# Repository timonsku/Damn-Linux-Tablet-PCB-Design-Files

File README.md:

DLT - A Damn Linux Tablet
==========
PCB Design Files
-----
Collection of PCB and CAD design files for DLT ( https://hackaday.io/project/164845-dlt-one-a-damn-linux-tablet ).
This project is currently in its early stages and none of the files hosted here are necessarily fully tested, they might work but only to the extent I need them to, some features that I have not tried might not work.
I uploaded them anyway at this stage for documentation purposes and for those that are curious.

All works are licensed under CC BY-SA 4.0.

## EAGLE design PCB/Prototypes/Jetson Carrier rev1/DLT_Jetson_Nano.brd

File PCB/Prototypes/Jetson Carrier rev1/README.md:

Be aware this a prototype!
====

This means there might be issues with this board.
All peripherals have been tested and are working on this revision, it is mostly based on AntMicros schematics of their open source carrier design.
Still, you might find something not working for you, no gurantees so proceed with caution.

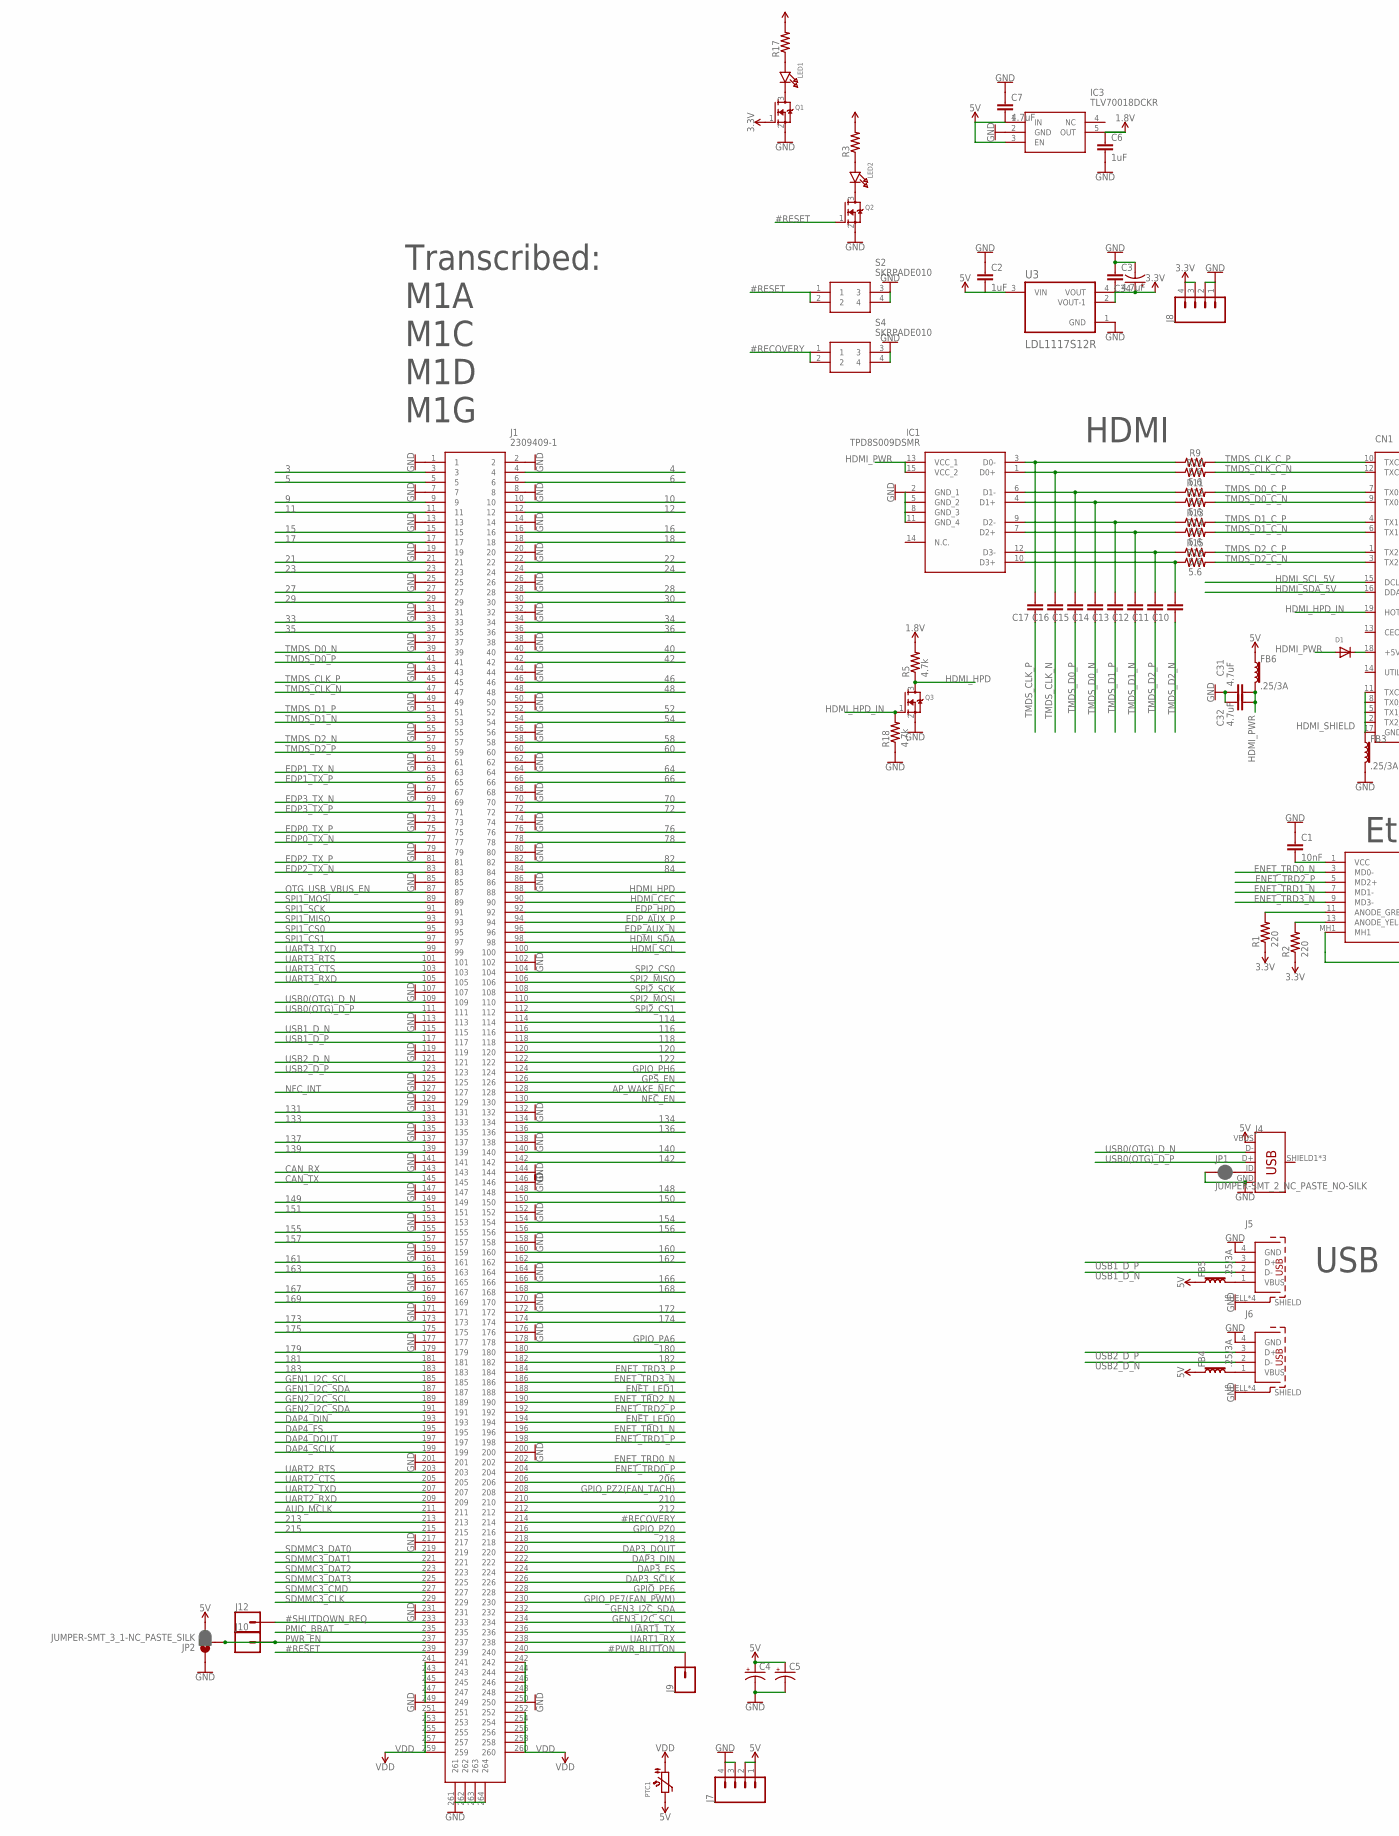
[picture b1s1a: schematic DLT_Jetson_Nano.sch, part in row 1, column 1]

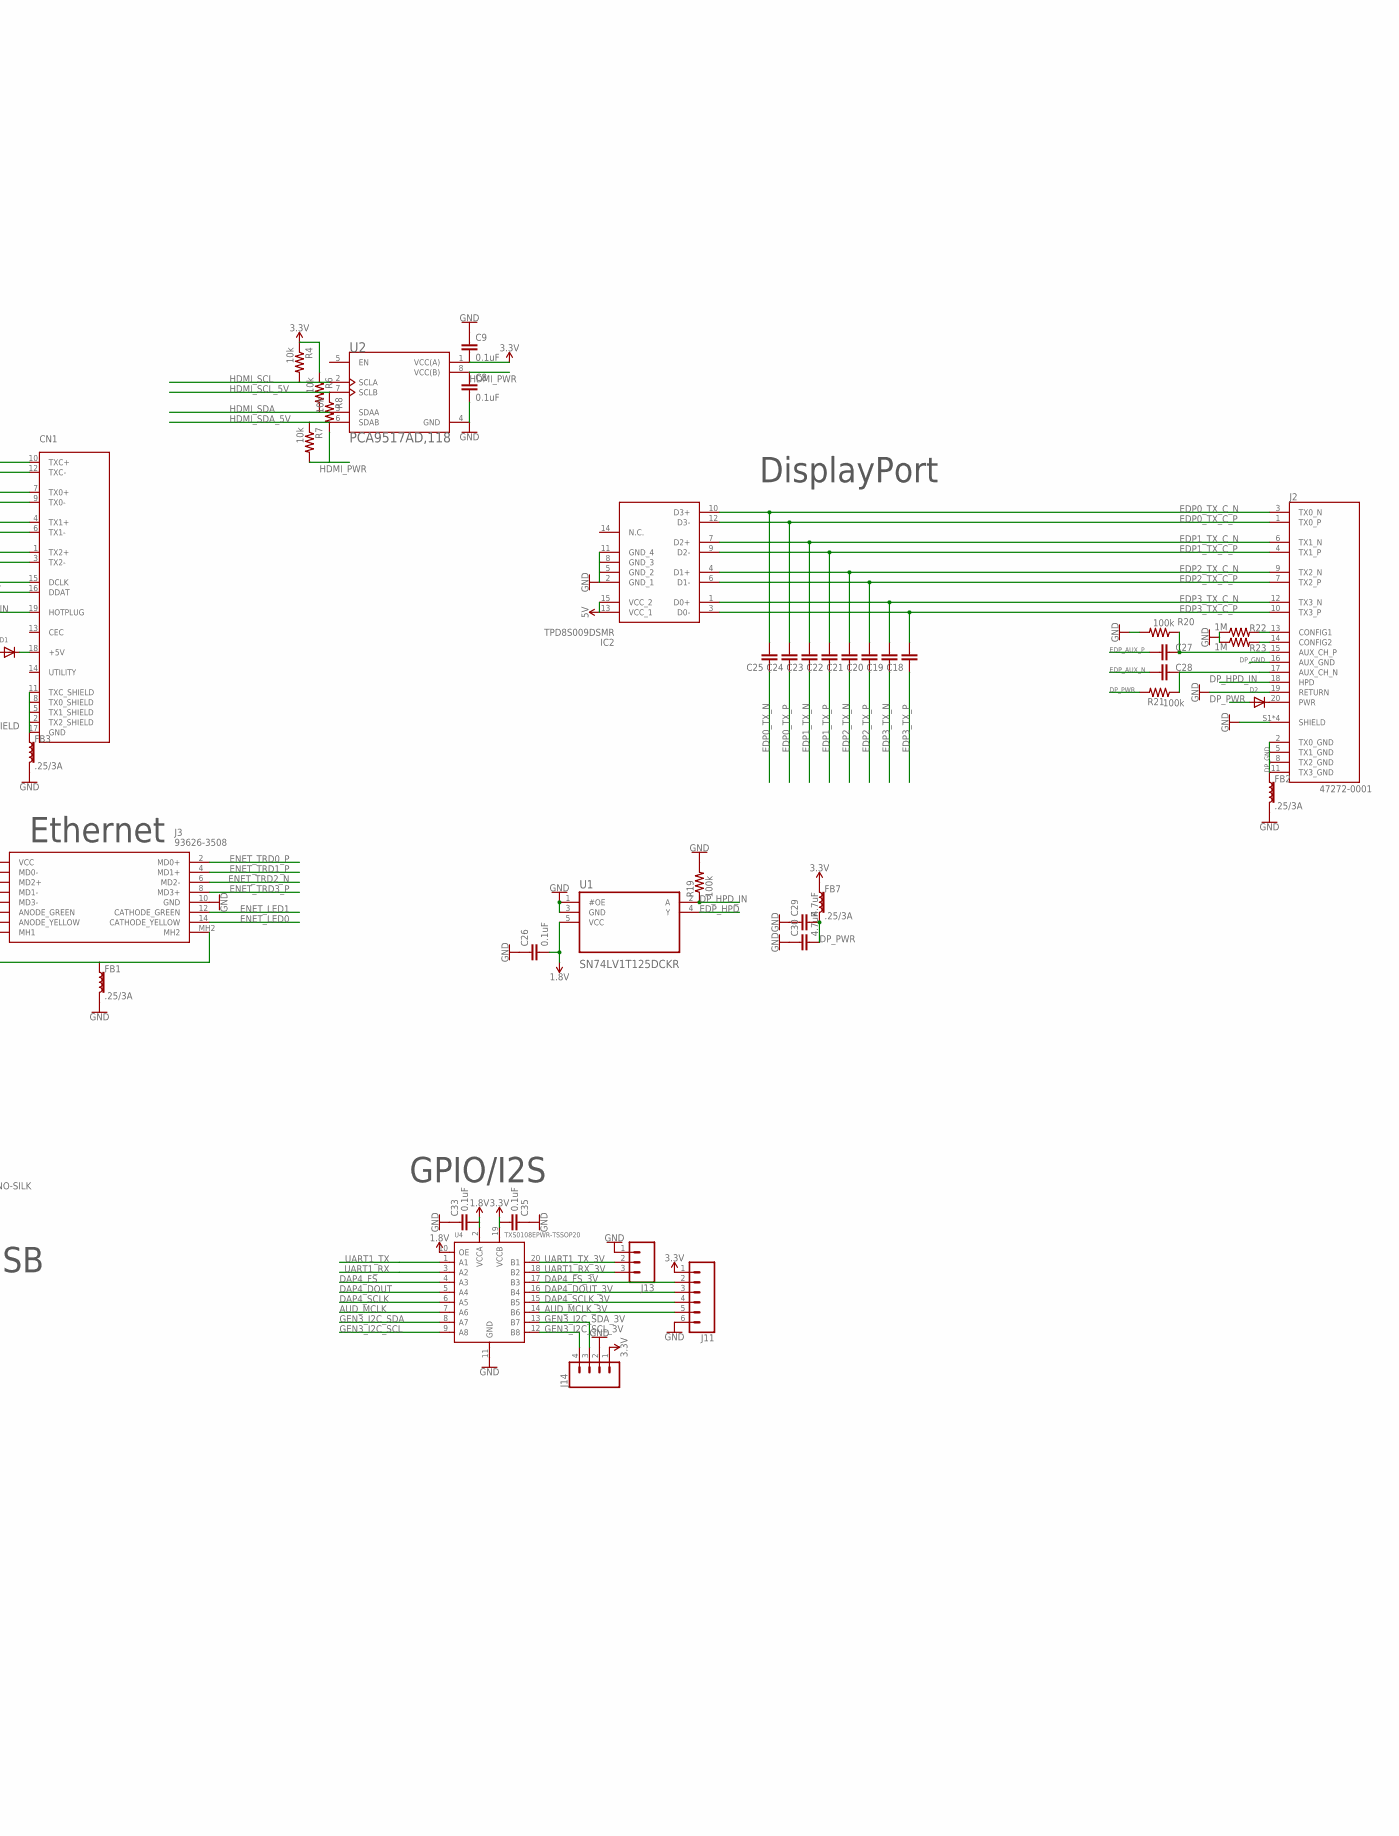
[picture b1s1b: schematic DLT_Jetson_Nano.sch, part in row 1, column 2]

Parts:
C1: 10nF; 0603
C2, C6: 1uF; 0603
C3, C7, C29, C30, C31, C32: 4.7uF; 0603
C4, C5, C34: CAP_POLD; PANASONIC_D
C8, C9, C26, C33, C35: 0.1uF; 0603
C10, C11, C12, C13, C14, C15, C16, C17, C18, C19, C20, C21, C22, C23, C24, C25, C27, C28: 0.1uF; 0402
CN1: HDMI_MOLEX_47151-0001
D1, D2: DIODESMA; SMADIODE
FB1, FB2, FB3, FB4, FB5, FB6, FB7: .25/3A; 0603
IC1, IC2: TPD8S009DSMR
IC3: TLV70018DCKR; SOT65P210X110-5N
J1: 2309409-1
J2: 47272-0001; MOLEX_47272-0001
J3: 93626-3508; 936263508
J4: USB_MICRO-B_FEMALE-SMT; USB-B-MICRO-SMD
J5, J6: 629104190121
J7, J8: CONN_04LOCK_LONGPADS; 1X04_LOCK_LONGPADS
J9, J10, J12: CONN_01; 1X01
J11: CONN_06SILK_FEMALE_PTH; 1X06
J13: CONN_03; 1X03
J14: CONN_04; 1X04
JP1: JUMPER-SMT_2_NC_PASTE_NO-SILK; SMT-JUMPER_2_NC_PASTE_NO-SILK
JP2: JUMPER-SMT_3_1-NC_PASTE_SILK; SMT-JUMPER_3_1-NC_PASTE_SILK
LED1, LED2: LED0805; CHIPLED_0805
PTC1: PTC1206; 1206
Q1, Q2, Q3: MOSFET-NWAVE; SOT23-W
R1, R2: 220; 0805
R3, R17: RESISTOR0805-RES; 0805
R4, R6, R7, R8: 10k; 0805
R5, R18: 4.7k; 0805
R9, R10, R11, R12, R13, R14, R15, R16: 5.6; 0402
R19, R20, R21: 100k; 0805
R22, R23: 1M; 0805
S2, S4: SKRPADE010
U1: SN74LV1T125DCKR; SOT65P210X110-5N
U2: PCA9517AD,118; SOIC127P600X175-8N
U3: LDL1117S12R; SOT230P700X180-4N
U4: TXS0108EPWR-TSSOP20; TSSOP20-0.65-6.5X4.4MM

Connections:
1.8V: C6.1, C26.2, C33.2, IC3.5 (OUT), R5.2, U1.5 (VCC), U4.2 (VCCA), U4.10 (OE)
3: J1.3
3.3V: C3.2, C9.2, C34.+, C35.1, FB7.1, J8.3, J8.4, J11.1, J14.1, Q1.1 (G), R1.1, R2.1, R4.1, R6.1, U2.1 (VCC(A)), U3.2 (VOUT-1), U3.4 (VOUT), U4.19 (VCCB)
4: J1.4
5: J1.5
5V: C2.2, C4.+, C5.+, C7.2, FB4.1, FB5.1, FB6.1, IC2.13 (VCC_1), IC2.15 (VCC_2), IC3.1 (IN), IC3.3 (EN), J4.VBUS, J7.1, J7.2, JP2.3, PTC1.2, R3.2, R17.2, U3.3 (VIN)
6: J1.6
9: J1.9
10: J1.10
11: J1.11
12: J1.12
15: J1.15
16: J1.16
17: J1.17
18: J1.18
21: J1.21
22: J1.22
23: J1.23
24: J1.24
27: J1.27
28: J1.28
29: J1.29
30: J1.30
33: J1.33
34: J1.34
35: J1.35
36: J1.36
40: J1.40
42: J1.42
46: J1.46
48: J1.48
52: J1.52
54: J1.54
58: J1.58
60: J1.60
64: J1.64
66: J1.66
70: J1.70
72: J1.72
76: J1.76
78: J1.78
82: J1.82
84: J1.84
114: J1.114
116: J1.116
118: J1.118
120: J1.120
122: J1.122
131: J1.131
133: J1.133
134: J1.134
136: J1.136
137: J1.137
139: J1.139
140: J1.140
142: J1.142
148: J1.148
149: J1.149
150: J1.150
151: J1.151
154: J1.154
155: J1.155
156: J1.156
157: J1.157
160: J1.160
161: J1.161
162: J1.162
163: J1.163
166: J1.166
167: J1.167
168: J1.168
169: J1.169
172: J1.172
173: J1.173
174: J1.174
175: J1.175
179: J1.179
180: J1.180
181: J1.181
182: J1.182
183: J1.183
206: J1.206
210: J1.210
212: J1.212
213: J1.213
215: J1.215
218: J1.218
#PWR_BUTTON: J1.240, J9.1
#RECOVERY: J1.214, S4.1, S4.2
#RESET: J1.239, Q2.1 (G), S2.1, S2.2
#SHUTDOWN_REQ: J1.233, J12.1
AP_WAKE_NFC: J1.128
AUD_MCLK: J1.211, U4.7 (A6)
AUD_MCLK_3V: J11.5, U4.14 (B6)
CAN_RX: J1.143
CAN_TX: J1.145
CONFIG1: J2.13 (CONFIG1), R22.2
CONFIG2: J2.14 (CONFIG2), R23.2
DAP3_DIN: J1.222
DAP3_DOUT: J1.220
DAP3_FS: J1.224
DAP3_SCLK: J1.226
DAP4_DIN: J1.193
DAP4_DOUT: J1.197, U4.5 (A4)
DAP4_DOUT_3V: J11.3, U4.16 (B4)
DAP4_FS: J1.195, U4.4 (A3)
DAP4_FS_3V: J11.2, U4.17 (B3)
DAP4_SCLK: J1.199, U4.6 (A5)
DAP4_SCLK_3V: J11.4, U4.15 (B5)
DP_GND: FB2.1, J2.2 (TX0_GND), J2.5 (TX1_GND), J2.8 (TX2_GND), J2.11 (TX3_GND), J2.16 (AUX_GND)
DP_HPD_IN: J2.18 (HPD), R19.1, U1.2 (A)
DP_PWR: C29.2, C30.2, D2.A, FB7.2, R21.2
EDP0_TX_C_N: C25.2, IC2.10 (D3+), J2.3 (TX0_N)
EDP0_TX_C_P: C24.2, IC2.12 (D3-), J2.1 (TX0_P)
EDP0_TX_N: C25.1, J1.77
EDP0_TX_P: C24.1, J1.75
EDP1_TX_C_N: C23.2, IC2.7 (D2+), J2.6 (TX1_N)
EDP1_TX_C_P: C22.2, IC2.9 (D2-), J2.4 (TX1_P)
EDP1_TX_N: C23.1, J1.63
EDP1_TX_P: C22.1, J1.65
EDP2_TX_C_N: C21.2, IC2.4 (D1+), J2.9 (TX2_N)
EDP2_TX_C_P: C20.2, IC2.6 (D1-), J2.7 (TX2_P)
EDP2_TX_N: C21.1, J1.83
EDP2_TX_P: C20.1, J1.81
EDP3_TX_C_N: C19.2, IC2.1 (D0+), J2.12 (TX3_N)
EDP3_TX_C_P: C18.2, IC2.3 (D0-), J2.10 (TX3_P)
EDP3_TX_N: C19.1, J1.69
EDP3_TX_P: C18.1, J1.71
EDP_AUX_C_N: C28.1, J2.17 (AUX_CH_N), R21.1
EDP_AUX_C_P: C27.1, J2.15 (AUX_CH_P), R20.1
EDP_AUX_N: C28.2, J1.96
EDP_AUX_P: C27.2, J1.94
EDP_HPD: J1.92, U1.4 (Y)
ENET_LED0: J1.194, J3.14 (CATHODE_YELLOW)
ENET_LED1: J1.188, J3.12 (CATHODE_GREEN)
ENET_TRD0_N: J1.202, J3.3 (MD0-)
ENET_TRD0_P: J1.204, J3.2 (MD0+)
ENET_TRD1_N: J1.196, J3.7 (MD1-)
ENET_TRD1_P: J1.198, J3.4 (MD1+)
ENET_TRD2_N: J1.190, J3.6 (MD2-)
ENET_TRD2_P: J1.192, J3.5 (MD2+)
ENET_TRD3_N: J1.186, J3.9 (MD3-)
ENET_TRD3_P: J1.184, J3.8 (MD3+)
GEN1_I2C_SCL: J1.185
GEN1_I2C_SDA: J1.187
GEN2_I2C_SCL: J1.189
GEN2_I2C_SDA: J1.191
GEN3_I2C_SCL: J1.234, U4.9 (A8)
GEN3_I2C_SCL_3V: J14.4, U4.12 (B8)
GEN3_I2C_SDA: J1.232, U4.8 (A7)
GEN3_I2C_SDA_3V: J14.3, U4.13 (B7)
GND: C1.1, C2.1, C3.1, C4.-, C5.-, C6.2, C7.1, C8.2, C9.1, C26.1, C29.1, C30.1, C31.1, C32.1, C33.1, C34.-, C35.2, CN1.P$1 (GND), CN1.P$2 (GND), CN1.P$3 (GND), CN1.P$4 (GND), FB1.2, FB2.2, FB3.2, IC1.2 (GND_1), IC1.5 (GND_2), IC1.8 (GND_3), IC1.11 (GND_4), IC2.2 (GND_1), IC2.5 (GND_2), IC2.8 (GND_3), IC2.11 (GND_4), IC3.2 (GND), J1.1, J1.2, J1.7, J1.8, J1.13, J1.14, J1.19, J1.20, J1.25, J1.26, J1.31, J1.32, J1.37, J1.38, J1.43, J1.44, J1.49, J1.50, J1.55, J1.56, J1.61, J1.62, J1.67, J1.68, J1.73, J1.74, J1.79, J1.80, J1.85, J1.86, J1.102, J1.107, J1.113, J1.119, J1.125, J1.129, J1.132, J1.135, J1.138, J1.141, J1.144, J1.146, J1.147, J1.152, J1.153, J1.158, J1.159, J1.164, J1.165, J1.170, J1.171, J1.176, J1.177, J1.200, J1.201, J1.217, J1.231, J1.241, J1.242, J1.243, J1.244, J1.245, J1.246, J1.247, J1.248, J1.249, J1.250, J1.261, J1.262, J1.263, J1.264, J2.19 (RETURN), J2.S1 (SHIELD), J2.S2 (SHIELD), J2.S3 (SHIELD), J2.S4 (SHIELD), J3.10 (GND), J4.GND, J5.4 (GND), J5.SHELL (SHIELD), J5.SHELL1 (SHIELD), J5.SHELL2 (SHIELD), J5.SHELL3 (SHIELD), J6.4 (GND), J6.SHELL (SHIELD), J6.SHELL1 (SHIELD), J6.SHELL2 (SHIELD), J6.SHELL3 (SHIELD), J7.3, J7.4, J8.1, J8.2, J11.6, J13.1, J14.2, JP1.1, JP2.1, Q1.2 (S), Q2.2 (S), Q3.2 (S), R18.1, R19.2, R20.2, R22.1, R23.1, S2.3, S2.4, S4.3, S4.4, U1.1 (#OE), U1.3 (GND), U2.4 (GND), U3.1 (GND), U4.11 (GND)
GPIO_PA6: J1.178
GPIO_PE6: J1.228
GPIO_PE7(FAN_PWM): J1.230
GPIO_PH6: J1.124
GPIO_PZ0: J1.216
GPIO_PZ2(FAN_TACH): J1.208
GPS_EN: J1.126
HDMI_5V_DIODE: CN1.18 (+5V), D1.C
HDMI_CEC: J1.90
HDMI_HPD: J1.88, Q3.3 (D), R5.1
HDMI_HPD_IN: CN1.19 (HOTPLUG), Q3.1 (G), R18.2
HDMI_PWR: C8.1, C31.2, C32.2, D1.A, FB6.2, IC1.13 (VCC_1), IC1.15 (VCC_2), R7.2, R8.2, U2.8 (VCC(B))
HDMI_SCL: J1.100, R4.2, U2.2 (SCLA)
HDMI_SCL_5V: CN1.15 (DCLK), R8.1, U2.7 (SCLB)
HDMI_SDA: J1.98, R6.2, U2.3 (SDAA)
HDMI_SDA_5V: CN1.16 (DDAT), R7.1, U2.6 (SDAB)
HDMI_SHIELD: CN1.2 (TX2_SHIELD), CN1.5 (TX1_SHIELD), CN1.8 (TX0_SHIELD), CN1.11 (TXC_SHIELD), CN1.17 (GND), FB3.1
unnamed: J3.11 (ANODE_GREEN), R1.2
unnamed: J3.13 (ANODE_YELLOW), R2.2
unnamed: C1.2, J3.1 (VCC)
unnamed: FB1.1, J3.MH1, J3.MH2
unnamed: LED2.C, Q2.3 (D)
unnamed: FB5.2, J5.1 (VBUS)
unnamed: FB4.2, J6.1 (VBUS)
unnamed: LED2.A, R3.1
unnamed: J4.ID, JP1.2
unnamed: LED1.C, Q1.3 (D)
unnamed: LED1.A, R17.1
unnamed: D2.C, J2.20 (PWR)
NFC_EN: J1.130
NFC_INT: J1.127
OTG_USB_VBUS_EN: J1.87
PMIC_BBAT: J1.235
PWR_EN: J1.237, J10.1, JP2.2
SDMMC3_CLK: J1.229
SDMMC3_CMD: J1.227
SDMMC3_DAT0: J1.219
SDMMC3_DAT1: J1.221
SDMMC3_DAT2: J1.223
SDMMC3_DAT3: J1.225
SPI1_CS0: J1.95
SPI1_CS1: J1.97
SPI1_MISO: J1.93
SPI1_MOSI: J1.89
SPI1_SCK: J1.91
SPI2_CS0: J1.104
SPI2_CS1: J1.112
SPI2_MISO: J1.106
SPI2_MOSI: J1.110
SPI2_SCK: J1.108
TMDS_CLK_C1_N: C16.2, IC1.1 (D0+), R10.1
TMDS_CLK_C1_P: C17.2, IC1.3 (D0-), R9.1
TMDS_CLK_C_N: CN1.12 (TXC-), R10.2
TMDS_CLK_C_P: CN1.10 (TXC+), R9.2
TMDS_CLK_N: C16.1, J1.47
TMDS_CLK_P: C17.1, J1.45
TMDS_D0_C1_N: C14.2, IC1.4 (D1+), R12.1
TMDS_D0_C1_P: C15.2, IC1.6 (D1-), R11.1
TMDS_D0_C_N: CN1.9 (TX0-), R12.2
TMDS_D0_C_P: CN1.7 (TX0+), R11.2
TMDS_D0_N: C14.1, J1.39
TMDS_D0_P: C15.1, J1.41
TMDS_D1_C1_N: C12.2, IC1.7 (D2+), R14.1
TMDS_D1_C1_P: C13.2, IC1.9 (D2-), R13.1
TMDS_D1_C_N: CN1.6 (TX1-), R14.2
TMDS_D1_C_P: CN1.4 (TX1+), R13.2
TMDS_D1_N: C12.1, J1.53
TMDS_D1_P: C13.1, J1.51
TMDS_D2_C1_N: C10.2, IC1.10 (D3+), R16.1
TMDS_D2_C1_P: C11.2, IC1.12 (D3-), R15.1
TMDS_D2_C_N: CN1.3 (TX2-), R16.2
TMDS_D2_C_P: CN1.1 (TX2+), R15.2
TMDS_D2_N: C10.1, J1.57
TMDS_D2_P: C11.1, J1.59
UART1_RX: J1.238, U4.3 (A2)
UART1_RX_3V: J13.3, U4.18 (B2)
UART1_TX: J1.236, U4.1 (A1)
UART1_TX_3V: J13.2, U4.20 (B1)
UART2_CTS: J1.205
UART2_RTS: J1.203
UART2_RXD: J1.209
UART2_TXD: J1.207
UART3_CTS: J1.103
UART3_RTS: J1.101
UART3_RXD: J1.105
UART3_TXD: J1.99
USB0(OTG)_D_N: J1.109, J4.D-
USB0(OTG)_D_P: J1.111, J4.D+
USB1_D_N: J1.115, J5.2 (D-)
USB1_D_P: J1.117, J5.3 (D+)
USB2_D_N: J1.121, J6.2 (D-)
USB2_D_P: J1.123, J6.3 (D+)
VDD: J1.251, J1.252, J1.253, J1.254, J1.255, J1.256, J1.257, J1.258, J1.259, J1.260, PTC1.1

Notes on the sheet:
Transcribed: M1A M1C M1D M1G
DisplayPort
HDMI
Ethernet
GPIO/I2S
USB

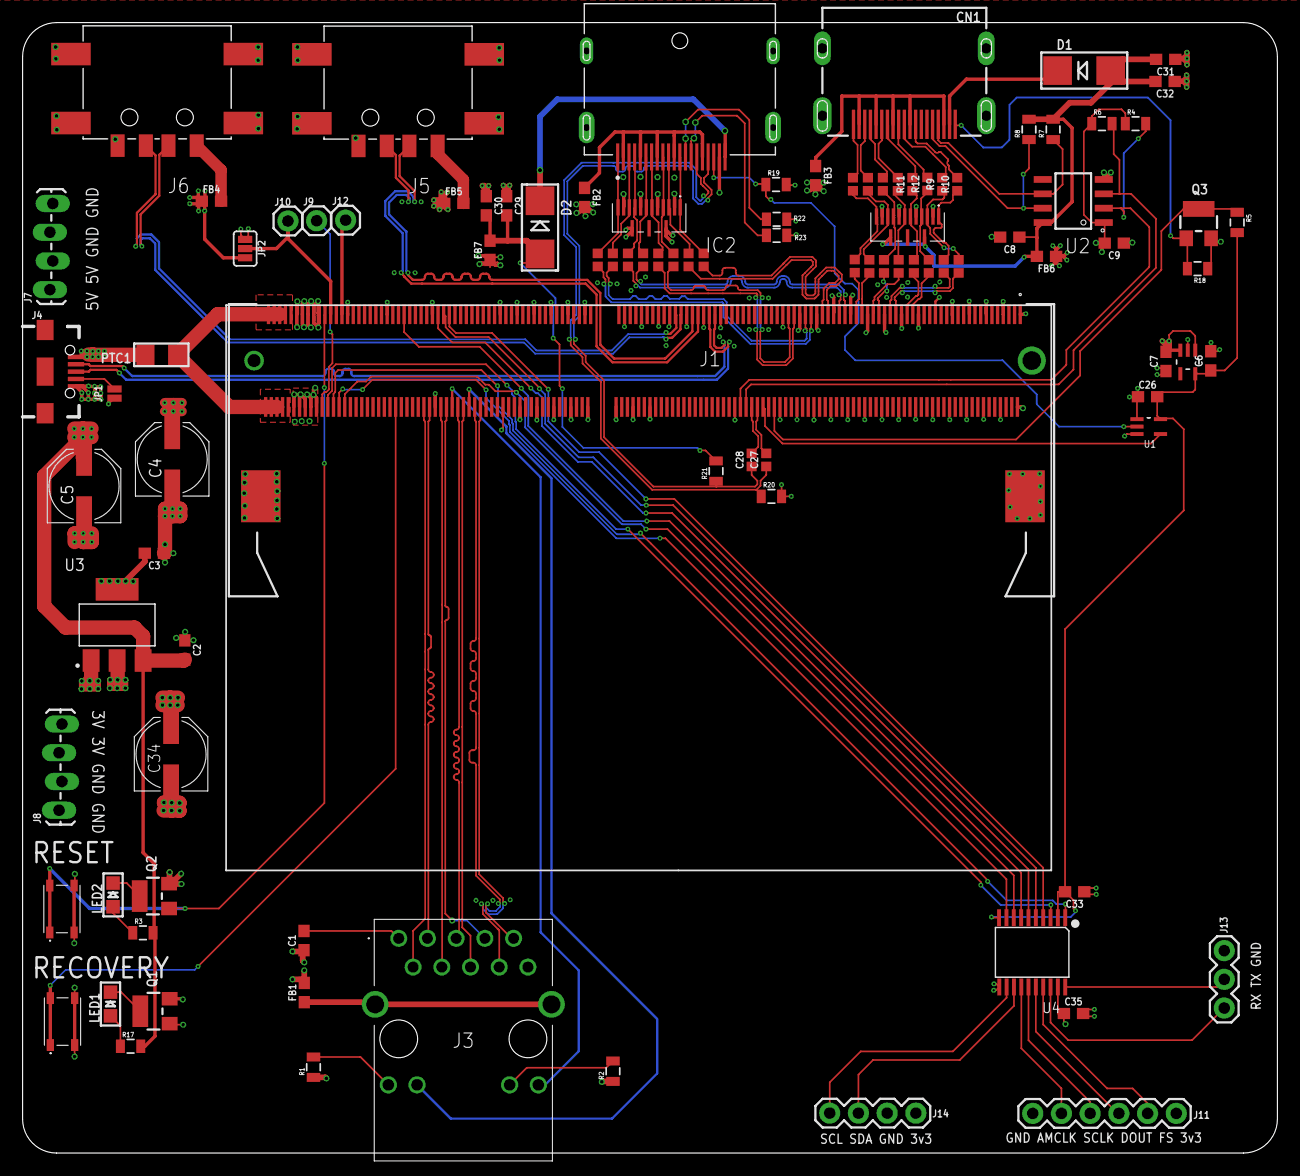
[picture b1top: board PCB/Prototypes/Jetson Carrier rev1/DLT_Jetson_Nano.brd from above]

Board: 4 copper layers, 111.0 x 100.0 mm, 99 parts (0 on the bottom side), 113 nets.

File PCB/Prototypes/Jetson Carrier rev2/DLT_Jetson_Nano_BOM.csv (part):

"Part";"Value";"Device";"Package";"Description";"AVAILABILITY";"DESCRIPTION";"HEIGHT";"MANUFACTURER_NAME";"MANUFACTURER_PART_NUMBER";"MF";"MOUSER_PART_NUMBER";"MOUSER_PRICE-STOCK";"MP";"PACKAGE";"PRICE";"PROD_ID";"VALUE";
"C2";"1uF";"10NF-0603-50V-10%";"0603";"0.01uF/10nF/10,000pF ceramic capacitors";"";"";"";"";"";"";"";"";"";"";"";"CAP-00867";"10nF";
"C3";"4.7uF";"10NF-0603-50V-10%";"0603";"0.01uF/10nF/10,000pF ceramic capacitors";"";"";"";"";"";"";"";"";"";"";"";"CAP-00867";"10nF";
"C4";"47uF";"47UF-POLAR-EIA3528-10V-10%";"EIA3528";"47µF polarized capacitors";"";"";"";"";"";"";"";"";"";"";"";"CAP-08310";"47uF";
"C5";"47uF";"47UF-POLAR-EIA3528-10V-10%";"EIA3528";"47µF polarized capacitors";"";"";"";"";"";"";"";"";"";"";"";"CAP-08310";"47uF";
"C6";"1uF";"10NF-0603-50V-10%";"0603";"0.01uF/10nF/10,000pF ceramic capacitors";"";"";"";"";"";"";"";"";"";"";"";"CAP-00867";"10nF";
"C7";"4.7uF";"10NF-0603-50V-10%";"0603";"0.01uF/10nF/10,000pF ceramic capacitors";"";"";"";"";"";"";"";"";"";"";"";"CAP-00867";"10nF";
"C10";"0.1uF";"0.1UF-0402-16V-10%";"0402";"0.1µF ceramic capacitors";"";"";"";"";"";"";"";"";"";"";"";"CAP-12416";"0.1uF";
"C11";"0.1uF";"0.1UF-0402-16V-10%";"0402";"0.1µF ceramic capacitors";"";"";"";"";"";"";"";"";"";"";"";"CAP-12416";"0.1uF";
"C12";"0.1uF";"0.1UF-0402-16V-10%";"0402";"0.1µF ceramic capacitors";"";"";"";"";"";"";"";"";"";"";"";"CAP-12416";"0.1uF";
"C13";"0.1uF";"0.1UF-0402-16V-10%";"0402";"0.1µF ceramic capacitors";"";"";"";"";"";"";"";"";"";"";"";"CAP-12416";"0.1uF";
"C14";"0.1uF";"0.1UF-0402-16V-10%";"0402";"0.1µF ceramic capacitors";"";"";"";"";"";"";"";"";"";"";"";"CAP-12416";"0.1uF";
"C15";"0.1uF";"0.1UF-0402-16V-10%";"0402";"0.1µF ceramic capacitors";"";"";"";"";"";"";"";"";"";"";"";"CAP-12416";"0.1uF";
"C16";"0.1uF";"0.1UF-0402-16V-10%";"0402";"0.1µF ceramic capacitors";"";"";"";"";"";"";"";"";"";"";"";"CAP-12416";"0.1uF";
"C17";"0.1uF";"0.1UF-0402-16V-10%";"0402";"0.1µF ceramic capacitors";"";"";"";"";"";"";"";"";"";"";"";"CAP-12416";"0.1uF";
"C18";"0.1uF";"0.1UF-0402-16V-10%";"0402";"0.1µF ceramic capacitors";"";"";"";"";"";"";"";"";"";"";"";"CAP-12416";"0.1uF";
"C19";"0.1uF";"0.1UF-0402-16V-10%";"0402";"0.1µF ceramic capacitors";"";"";"";"";"";"";"";"";"";"";"";"CAP-12416";"0.1uF";
"C20";"0.1uF";"0.1UF-0402-16V-10%";"0402";"0.1µF ceramic capacitors";"";"";"";"";"";"";"";"";"";"";"";"CAP-12416";"0.1uF";
"C21";"0.1uF";"0.1UF-0402-16V-10%";"0402";"0.1µF ceramic capacitors";"";"";"";"";"";"";"";"";"";"";"";"CAP-12416";"0.1uF";
"C22";"0.1uF";"0.1UF-0402-16V-10%";"0402";"0.1µF ceramic capacitors";"";"";"";"";"";"";"";"";"";"";"";"CAP-12416";"0.1uF";
"C23";"0.1uF";"0.1UF-0402-16V-10%";"0402";"0.1µF ceramic capacitors";"";"";"";"";"";"";"";"";"";"";"";"CAP-12416";"0.1uF";
"C24";"0.1uF";"0.1UF-0402-16V-10%";"0402";"0.1µF ceramic capacitors";"";"";"";"";"";"";"";"";"";"";"";"CAP-12416";"0.1uF";
"C25";"0.1uF";"0.1UF-0402-16V-10%";"0402";"0.1µF ceramic capacitors";"";"";"";"";"";"";"";"";"";"";"";"CAP-12416";"0.1uF";
"C27";"0.1uF";"0.1UF-0402-16V-10%";"0402";"0.1µF ceramic capacitors";"";"";"";"";"";"";"";"";"";"";"";"CAP-12416";"0.1uF";
"C28";"0.1uF";"0.1UF-0402-16V-10%";"0402";"0.1µF ceramic capacitors";"";"";"";"";"";"";"";"";"";"";"";"CAP-12416";"0.1uF";
"C29";"4.7uF";"10NF-0603-50V-10%";"0603";"0.01uF/10nF/10,000pF ceramic capacitors";"";"";"";"";"";"";"";"";"";"";"";"CAP-00867";"10nF";
"C30";"4.7uF";"10NF-0603-50V-10%";"0603";"0.01uF/10nF/10,000pF ceramic capacitors";"";"";"";"";"";"";"";"";"";"";"";"CAP-00867";"10nF";
"C31";"4.7uF";"10NF-0603-50V-10%";"0603";"0.01uF/10nF/10,000pF ceramic capacitors";"";"";"";"";"";"";"";"";"";"";"";"CAP-00867";"10nF";
"C32";"4.7uF";"10NF-0603-50V-10%";"0603";"0.01uF/10nF/10,000pF ceramic capacitors";"";"";"";"";"";"";"";"";"";"";"";"CAP-00867";"10nF";
"C34";"47uF";"47UF-POLAR-EIA3528-10V-10%";"EIA3528";"47µF polarized capacitors";"";"";"";"";"";"";"";"";"";"";"";"CAP-08310";"47uF";
"CN1";"";"JST_2PIN-SMT-RA";"JST-PH-2-SMT-RA";"JST 2-Pin Connectors of various flavors";"";"";"";"";"";"";"";"";"";"";"";"";"";
"CN2";"";"JST_2PIN-SMT-RA";"JST-PH-2-SMT-RA";"JST 2-Pin Connectors of various flavors";"";"";"";"";"";"";"";"";"";"";"";"";"";
"FB2";".25/3A";"FERRITE_BEAD-0603";"0603";"Ferrite Bead (blocks, cores, rings, chokes, etc.)";"";"";"";"";"";"";"";"";"";"";"";"NDUC-13805";"30Ω/1.8A";
"FB3";".25/3A";"FERRITE_BEAD-0603";"0603";"Ferrite Bead (blocks, cores, rings, chokes, etc.)";"";"";"";"";"";"";"";"";"";"";"";"NDUC-13805";"30Ω/1.8A";
"FB6";".25/3A";"FERRITE_BEAD-0603";"0603";"Ferrite Bead (blocks, cores, rings, chokes, etc.)";"";"";"";"";"";"";"";"";"";"";"";"NDUC-13805";"30Ω/1.8A";
"FB7";".25/3A";"FERRITE_BEAD-0603";"0603";"Ferrite Bead (blocks, cores, rings, chokes, etc.)";"";"";"";"";"";"";"";"";"";"";"";"NDUC-13805";"30Ω/1.8A";
"IC1";"TPD8S009DSMR";"TPD8S009DSMR";"TPD8S009DSMR";"8-Channel ESD Solution for HDMI/DisplayPort";"";"8-Channel ESD Solution for HDMI/DisplayPort";"0mm";"Texas Instruments";"TPD8S009DSMR";"";"595-TPD8S009DSMR";"https://www.mouser.com/Search/Refine.aspx?Keyword=595-TPD8S009DSMR";"";"";"";"";"";
"IC2";"TPD8S009DSMR";"TPD8S009DSMR";"TPD8S009DSMR";"8-Channel ESD Solution for HDMI/DisplayPort";"";"8-Channel ESD Solution for HDMI/DisplayPort";"0mm";"Texas Instruments";"TPD8S009DSMR";"";"595-TPD8S009DSMR";"https://www.mouser.com/Search/Refine.aspx?Keyword=595-TPD8S009DSMR";"";"";"";"";"";
"IC3";"TLV70018DCKR";"TLV70018DCKR";"SOT65P210X110-5N";"200-mA, Low-IQ, Low-Dropout Regulator for Portable Devices";"";"200-mA, Low-IQ, Low-Dropout Regulator for Portable Devices";"mm";"Texas Instruments";"TLV70018DCKR";"";"595-TLV70018DCKR";"https://www.mouser.com/Search/Refine.aspx?Keyword=595-TLV70018DCKR";"";"";"";"";"";
"J1";"2309409-1";"2309409-1";"2309409-1";"TE CONNECTIVITY - 2309409-1 - CONN, DDR4 SODIMM SOCKET, 260POS, 0.5MM";"";"TE CONNECTIVITY - 2309409-1 - CONN, DDR4 SODIMM SOCKET, 260POS, 0.5MM";"mm";"TE Connectivity";"2309409-1";"";"571-2309409-1";"https://www.mouser.com/Search/Refine.aspx?Keyword=571-2309409-1";"";"";"";"";"";
"J2";"54132-3062";"54132-3062";"54132-3062";"Connector 0.5mm, FFC/FPC, SMT,r/a,30w,Au Molex FFC/FPC SMT Series 0.5mm Pitch 30 Way Right Angle SMT Female FPC Connector, ZIF Bottom Contact";"";"Connector 0.5mm, FFC/FPC, SMT,r/a,30w,Au Molex FFC/FPC SMT Series 0.5mm Pitch 30 Way Right Angle SMT Female FPC Connector, ZIF Bottom Contact";"mm";"Molex";"54132-3062";"";"538-54132-3062";"https://www.mouser.com/Search/Refine.aspx?Keyword=538-54132-3062";"";"";"";"";"";
"J3";"505110-1092";"505110-1092";"5051101092";"Molex Easy-On Series 0.5mm Pitch 10 Way Right Angle SMT Male FPC Connector, ZIF Bottom Contact";"";"Molex Easy-On Series 0.5mm Pitch 10 Way Right Angle SMT Male FPC Connector, ZIF Bottom Contact";"0mm";"Molex";"505110-1092";"";"538-505110-1092";"https://www.mouser.com/Search/Refine.aspx?Keyword=538-505110-1092";"";"";"";"";"";
"J4";"505110-1092";"505110-1092";"5051101092";"Molex Easy-On Series 0.5mm Pitch 10 Way Right Angle SMT Male FPC Connector, ZIF Bottom Contact";"";"Molex Easy-On Series 0.5mm Pitch 10 Way Right Angle SMT Male FPC Connector, ZIF Bottom Contact";"0mm";"Molex";"505110-1092";"";"538-505110-1092";"https://www.mouser.com/Search/Refine.aspx?Keyword=538-505110-1092";"";"";"";"";"";
"J5";"505110-1092";"505110-1092";"5051101092";"Molex Easy-On Series 0.5mm Pitch 10 Way Right Angle SMT Male FPC Connector, ZIF Bottom Contact";"";"Molex Easy-On Series 0.5mm Pitch 10 Way Right Angle SMT Male FPC Connector, ZIF Bottom Contact";"0mm";"Molex";"505110-1092";"";"538-505110-1092";"https://www.mouser.com/Search/Refine.aspx?Keyword=538-505110-1092";"";"";"";"";"";
"J6";"";"CONN_01";"1X01";"Single connection point. Often used as Generic Header-pin footprint for 0.1 inch spaced/style header connections";"";"";"";"";"";"";"";"";"";"";"";"";"";
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
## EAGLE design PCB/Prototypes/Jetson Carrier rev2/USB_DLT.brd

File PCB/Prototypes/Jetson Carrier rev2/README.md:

WORK IN PROGRESS
======
This is based of the first revision though some things are not working as expected at the moment so please do not produce any of these boards or base your own boards off this revision, they are here for documentation only!

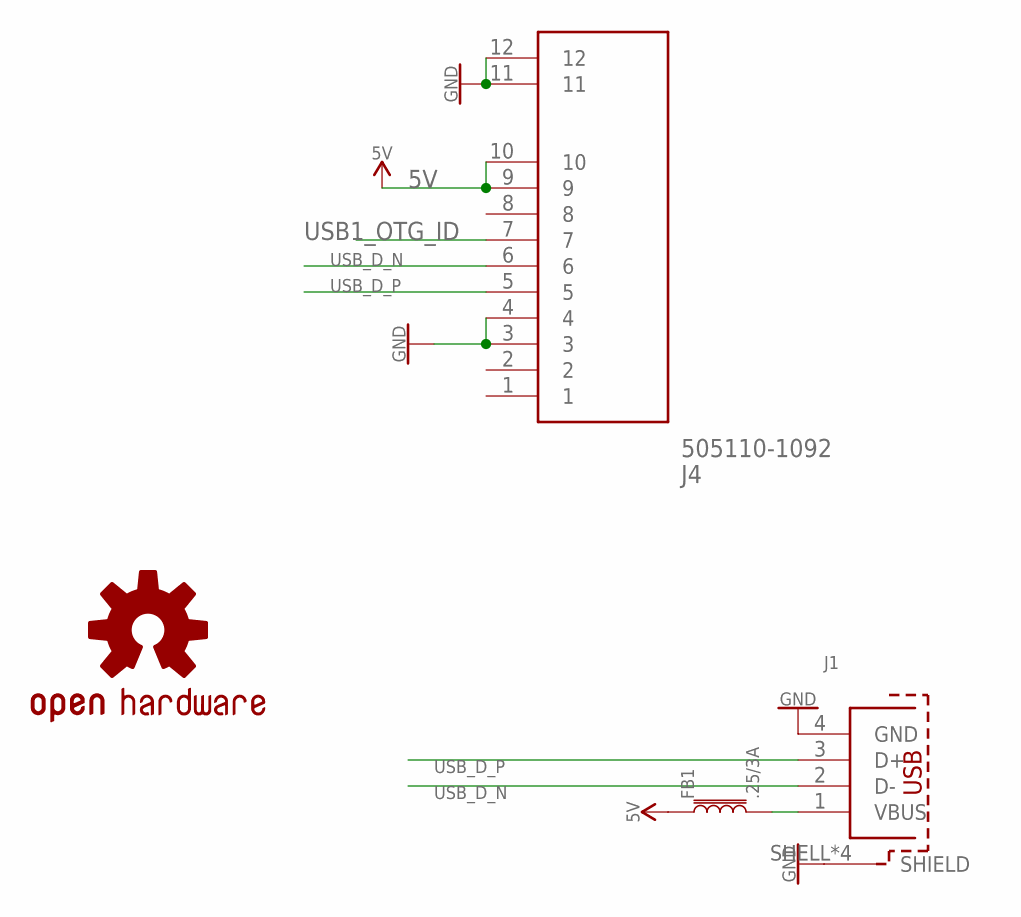
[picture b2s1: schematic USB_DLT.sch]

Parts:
FB1: .25/3A; 0603
J1: 629104190121
J4: 505110-1092; 5051101092
LOGO1: OSHW-LOGOS-COPPER; OSHW-LOGO-S_COPPER

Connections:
5V: FB1.1, J4.9, J4.10
5V_FB: FB1.2, J1.1 (VBUS)
GND: J1.4 (GND), J1.SHELL (SHIELD), J1.SHELL1 (SHIELD), J1.SHELL2 (SHIELD), J1.SHELL3 (SHIELD), J4.3, J4.4, J4.11, J4.12
USB1_OTG_ID: J4.7
USB_D_N: J1.2 (D-), J4.6
USB_D_P: J1.3 (D+), J4.5

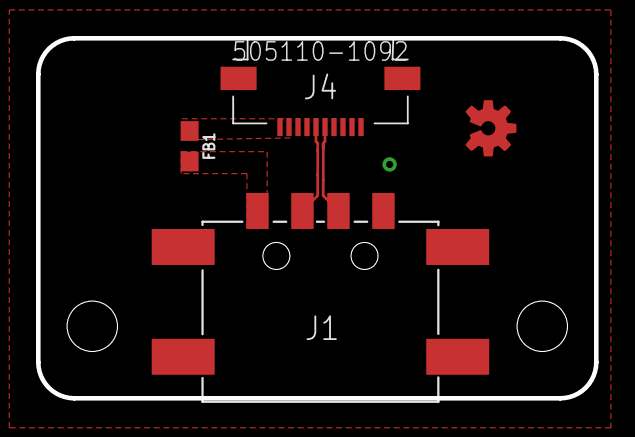
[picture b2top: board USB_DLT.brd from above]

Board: 2 copper layers, 31.0 x 20.0 mm, 4 parts (0 on the bottom side), 5 nets.

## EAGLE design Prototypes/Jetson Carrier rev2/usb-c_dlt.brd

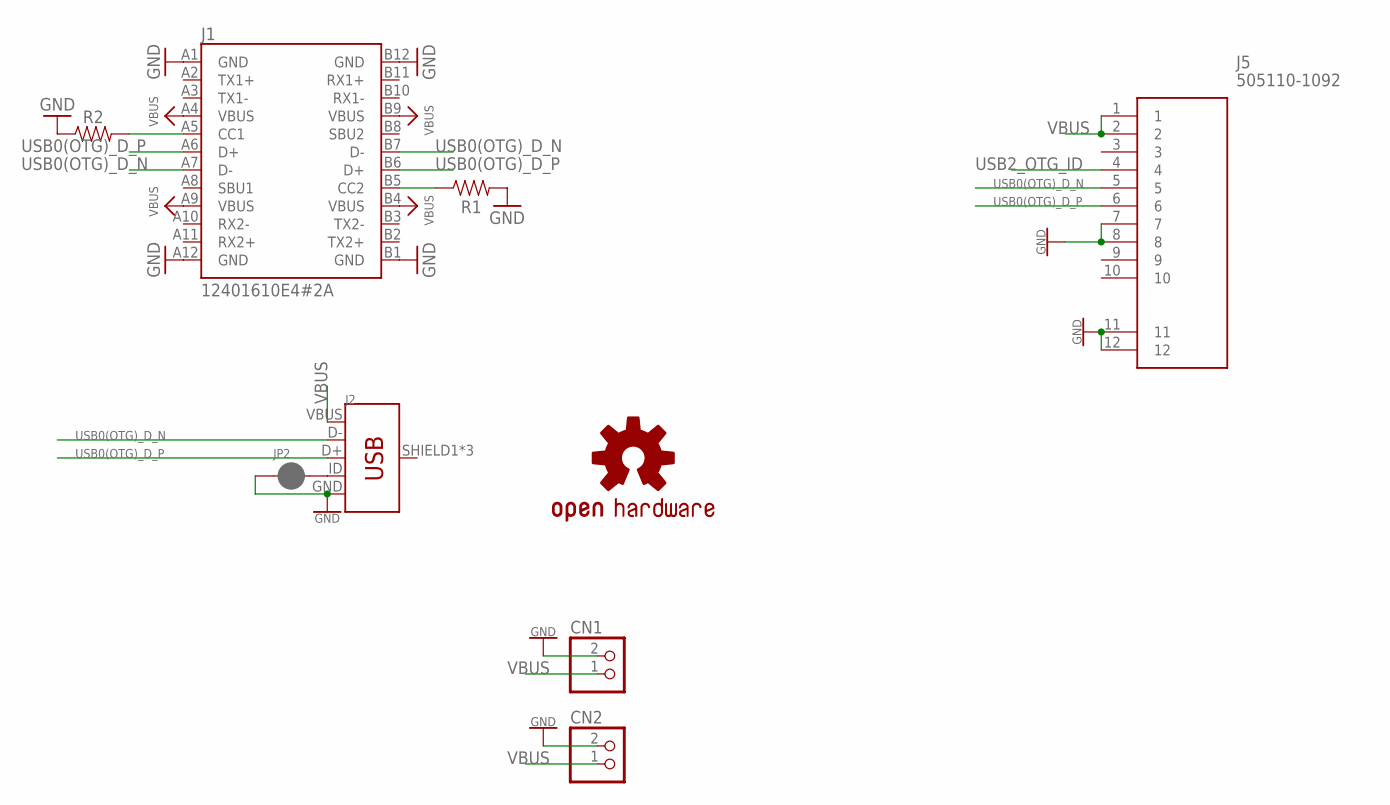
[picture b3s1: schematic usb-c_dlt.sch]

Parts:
CN1, CN2: JST_2PIN-SMT-RA; JST-PH-2-SMT-RA
J1: 12401610E4#2A; AMPHENOL_12401610E4#2A
J2: USB_MICRO-B_FEMALE-SMT; USB-B-MICRO-SMD
J5: 505110-1092; 5051101092
JP2: JUMPER-SMT_2_NC_PASTE_NO-SILK; SMT-JUMPER_2_NC_PASTE_NO-SILK
LOGO1: OSHW-LOGOS-COPPER; OSHW-LOGO-S_COPPER
R1, R2: 0603

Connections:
A0/CC2: J1.A5 (CC1), R2.2
A3/CC1: J1.B5 (CC2), R1.1
GND: CN1.2 (1), CN2.2 (1), J1.A1 (GND), J1.A12 (GND), J1.B1 (GND), J1.B12 (GND), J2.GND, J5.7, J5.8, J5.11, J5.12, JP2.1, R1.2, R2.1
unnamed: J2.ID, JP2.2
USB0(OTG)_D_N: J1.A7 (D-), J1.B7 (D-), J2.D-, J5.5
USB0(OTG)_D_P: J1.A6 (D+), J1.B6 (D+), J2.D+, J5.6
USB2_OTG_ID: J5.4
VBUS: CN1.1 (2), CN2.1 (2), J1.A4 (VBUS), J1.A9 (VBUS), J1.B4 (VBUS), J1.B9 (VBUS), J2.VBUS, J5.1, J5.2

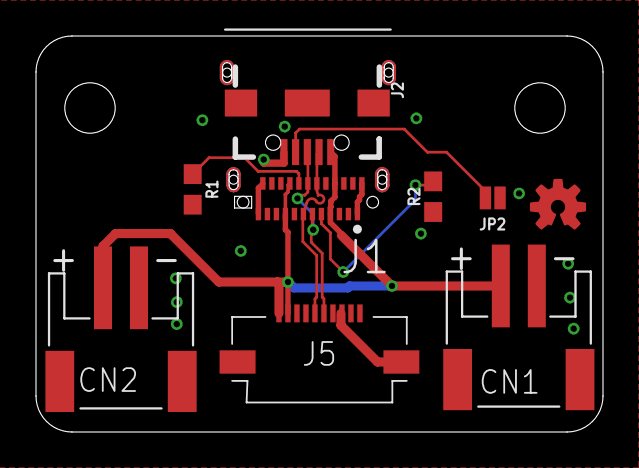
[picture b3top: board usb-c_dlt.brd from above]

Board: 2 copper layers, 31.5 x 22.0 mm, 9 parts (0 on the bottom side), 7 nets.

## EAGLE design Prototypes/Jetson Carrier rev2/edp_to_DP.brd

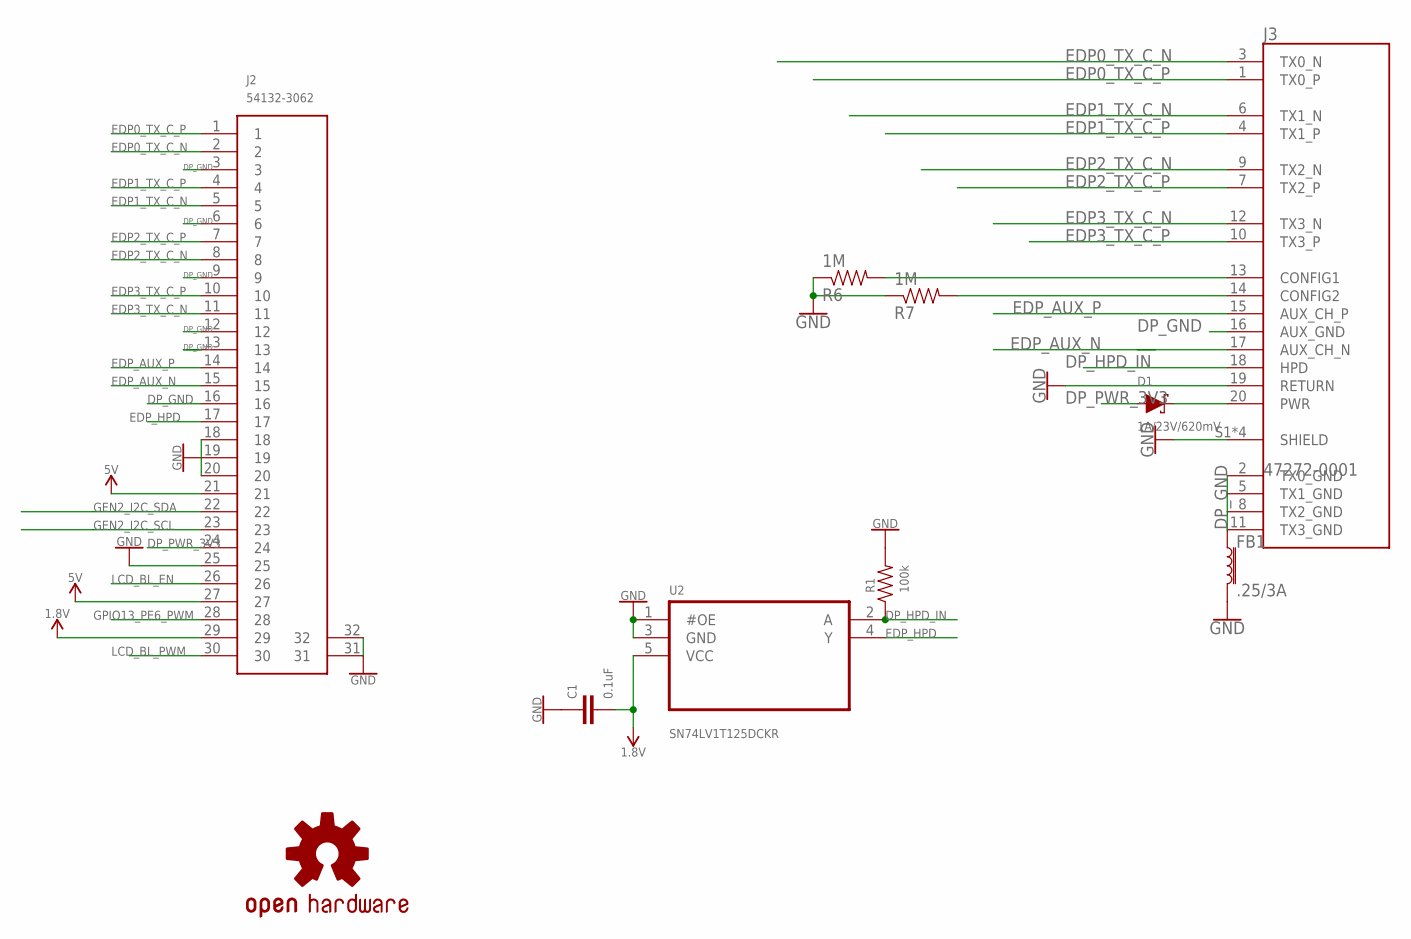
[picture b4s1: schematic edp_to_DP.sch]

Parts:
C1: 0.1uF; 0603
D1: 1A/23V/620mV; SOD-323
FB1: .25/3A; 0603
J2: 54132-3062
J3: 47272-0001; MOLEX_47272-0001
LOGO1: OSHW-LOGOS-COPPER; OSHW-LOGO-S_COPPER
R1: 100k; 0805
R6, R7: 1M; 0805
U2: SN74LV1T125DCKR; SOT65P210X110-5N

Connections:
1.8V: C1.2, J2.29, U2.5 (VCC)
3V3: D1.C, J3.20 (PWR)
5V: J2.21, J2.27
CONFIG3: J3.13 (CONFIG1), R6.2
CONFIG4: J3.14 (CONFIG2), R7.2
DP_GND: FB1.1, J2.3, J2.6, J2.9, J2.12, J2.13, J2.16, J3.2 (TX0_GND), J3.5 (TX1_GND), J3.8 (TX2_GND), J3.11 (TX3_GND), J3.16 (AUX_GND)
DP_HPD_IN: J3.18 (HPD), R1.1, U2.2 (A)
DP_PWR_3V3: D1.A, J2.24
EDP0_TX_C_N: J2.2, J3.3 (TX0_N)
EDP0_TX_C_P: J2.1, J3.1 (TX0_P)
EDP1_TX_C_N: J2.5, J3.6 (TX1_N)
EDP1_TX_C_P: J2.4, J3.4 (TX1_P)
EDP2_TX_C_N: J2.8, J3.9 (TX2_N)
EDP2_TX_C_P: J2.7, J3.7 (TX2_P)
EDP3_TX_C_N: J2.11, J3.12 (TX3_N)
EDP3_TX_C_P: J2.10, J3.10 (TX3_P)
EDP_AUX_N: J2.15, J3.17 (AUX_CH_N)
EDP_AUX_P: J2.14, J3.15 (AUX_CH_P)
EDP_HPD: J2.17, U2.4 (Y)
GEN2_I2C_SCL: J2.23
GEN2_I2C_SDA: J2.22
GND: C1.1, FB1.2, J2.18, J2.19, J2.20, J2.25, J2.31, J2.32, J3.19 (RETURN), J3.S1 (SHIELD), J3.S2 (SHIELD), J3.S3 (SHIELD), J3.S4 (SHIELD), R1.2, R6.1, R7.1, U2.1 (#OE), U2.3 (GND)
GPIO13_PE6_PWM: J2.28
LCD_BL_EN: J2.26
LCD_BL_PWM: J2.30

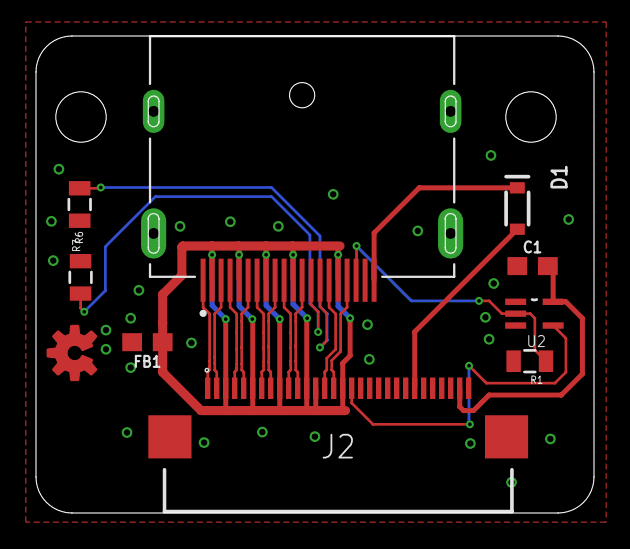
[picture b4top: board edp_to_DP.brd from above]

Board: 4 copper layers, 31.0 x 26.5 mm, 10 parts (0 on the bottom side), 20 nets.

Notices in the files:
parts and their libraries:
SparkFun-Passives: Licensing: Creative Commons ShareAlike 4.0 International - https://creativecommons.org/licenses/by-sa/4.0
microbuilder: This work is placed in the public domain, and may be freely used for commercial and non-commercial work with the following conditions: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
